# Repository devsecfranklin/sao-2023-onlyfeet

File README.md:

# badge-project-template

The docs and some other files have been sanitized from this repo.

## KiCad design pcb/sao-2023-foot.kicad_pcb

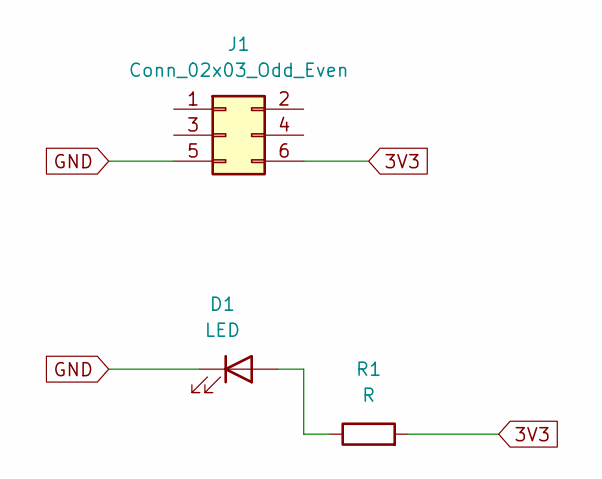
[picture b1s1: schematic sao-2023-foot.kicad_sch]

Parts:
D1: LED; LED_PLCC-2_Reverse-Mount
J1: Conn_02x03_Odd_Even; PinHeader_2x03_P2.54mm_Vertical_SMD
R1: R; R_1206_3216Metric_Pad1.30x1.75mm_HandSolder

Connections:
3V3: J1.6, R1.2
GND: D1.1 (K), J1.5
unnamed: D1.2 (A), R1.1

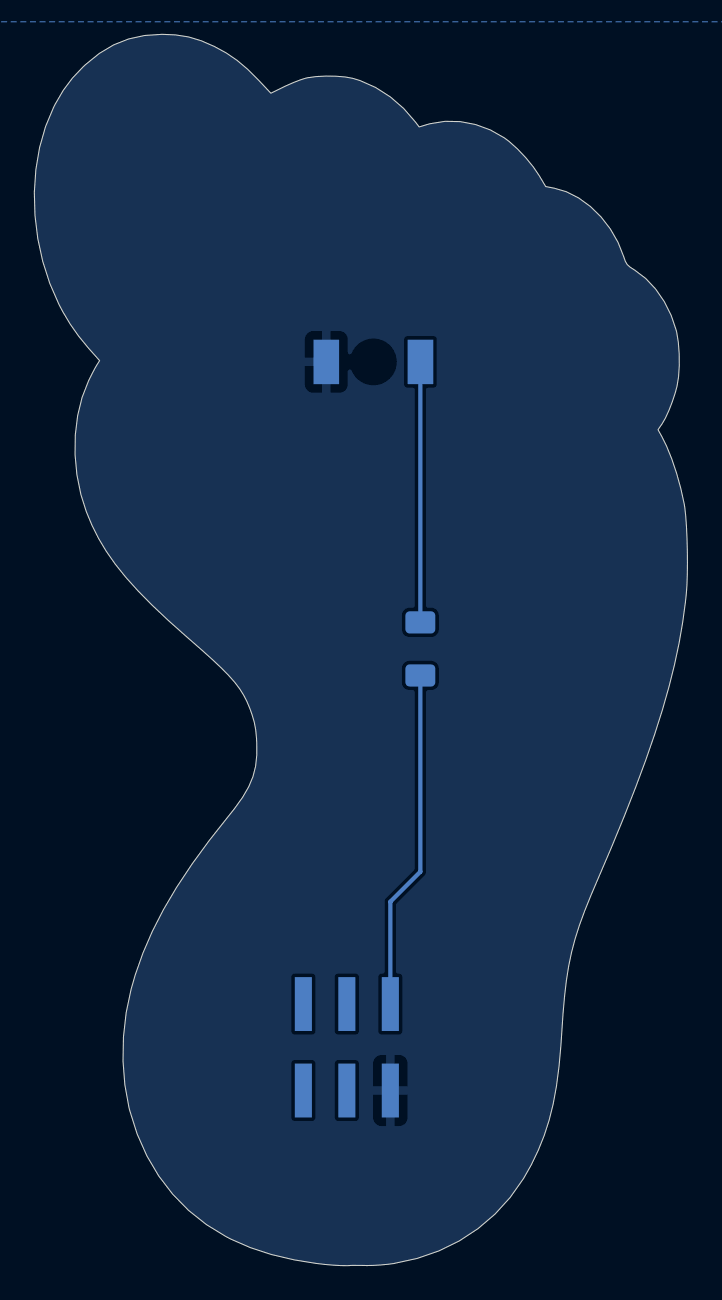
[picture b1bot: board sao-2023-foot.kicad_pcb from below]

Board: 2 copper layers, 38.1 x 71.9 mm, 3 parts (3 on the bottom side), 3 nets.

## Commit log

2023-06-12 first attempt
2023-06-12 clean up the repo
2023-06-12 remove extra stuff
2023-06-12 first attempt (#2)
    * first attempt
    * clean up the repo
    * remove extra stuff
2023-06-12 Add .whitesource configuration file
2023-06-12 Add .whitesource configuration file (#3)
2023-06-12 Now with KUBERNETES!
2023-06-13 Corrected SAO Connector
2023-06-13 Corrected SAO Connector (#4)
2023-06-14 update some art
2023-06-14 update some art (#5)
    * update some art
    * update some art
2023-07-21 Update fsfe/reuse-action action to v1.3.0 (#6)
2023-07-21 Update fsfe/reuse-action action to v2
2023-07-21 Update fsfe/reuse-action action to v2 (#7)
2023-10-19 Update actions/checkout action to v4
2024-02-27 Update fsfe/reuse-action action to v3
2024-05-24 Update actions/checkout action to v4 (#8)
2024-05-24 Update fsfe/reuse-action action to v3 (#9)
2024-05-24 add more art
2024-07-03 Update fsfe/reuse-action action to v4
2024-11-14 Update fsfe/reuse-action action to v5
2025-06-10 Update fsfe/reuse-action action to v5 (#12)
2025-06-10 Update nosborn/github-action-markdown-cli action to v3.4.0 (#13)
2025-06-10 add more art (#10)
2025-08-11 Update actions/checkout action to v5
2025-08-24 Update actions/checkout action to v5 (#16)
2025-08-24 Update nosborn/github-action-markdown-cli action to v3.5.0 (#15)
2025-08-24 Update README.md (#14)
